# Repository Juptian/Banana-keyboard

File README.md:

# banana
* Keyboard Maintainer: [Sebastien Gosselin](https://github.com/Juptian)
* Custom PCB, built on an arduino promicro ATmega32u4
* Hardware Availability: Aliexpress has some go you'll find them for cheap

Make example for this keyboard (after setting up your build environment):

    make banana:default

Flashing example for this keyboard:

    make banana:default:flash

See the [build environment setup](https://docs.qmk.fm/#/getting_started_build_tools) and the [make instructions](https://docs.qmk.fm/#/getting_started_make_guide) for more information. Brand new to QMK? Start with our [Complete Newbs Guide](https://docs.qmk.fm/#/newbs).

## Bootloader

Enter the bootloader in 1 way:

* **Physical reset button**: Briefly press the button on the back of the PCB - some may have pads you must short instead

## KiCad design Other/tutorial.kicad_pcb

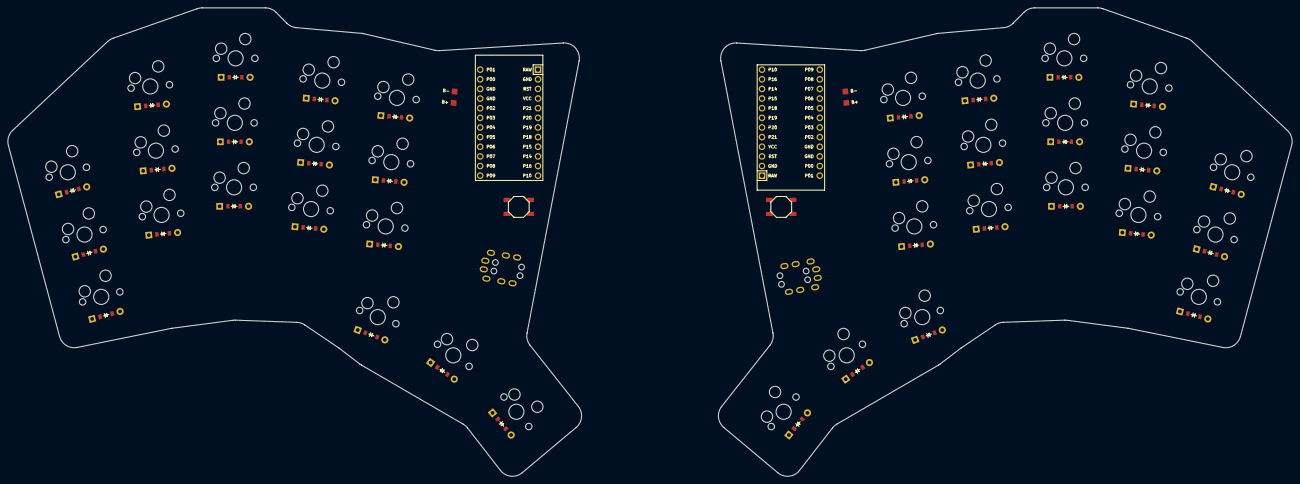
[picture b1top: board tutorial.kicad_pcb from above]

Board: 2 copper layers, 338.5 x 123.5 mm, 82 parts (0 on the bottom side), 58 nets, no tracks yet.

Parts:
B1, B2: SW_TACT_ALPS_SKQGABE010
D1, D2, D3, D4, D5, D6, D7, D8, D9, D10, D11, D12, D13, D14, D15, D16, D17, D18, D19, D20, D21, D22, D23, D24, D25, D26, D27, D28, D29, D30, D31, D32, D33, D34, D35, D36: ComboDiode
MCU1, MCU2: ProMicro
PAD1, PAD2, PAD3, PAD4: SMDPad
S1, S2, S3, S4, S5, S6, S7, S8, S9, S10, S11, S12, S13, S14, S15, S16, S17, S18, S19, S20, S21, S22, S23, S24, S25, S26, S27, S28, S29, S30, S31, S32, S33, S34, S35, S36: MX
TRRS1, TRRS2: TRRS-PJ-320A-dual

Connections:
Bplus: PAD1.1, PAD3.1
GND: B1.1, B2.1, MCU1.2, MCU1.15, MCU1.16, MCU2.2, MCU2.15, MCU2.16, PAD2.1, PAD4.1, TRRS1.3, TRRS2.3
P0: MCU1.14, MCU2.14, TRRS1.4, TRRS2.4
P1: MCU1.13, MCU2.13
P2: MCU1.17, MCU2.17
P8: MCU1.23, MCU2.23
P9: MCU1.24, MCU2.24
P10: MCU1.12, MCU2.12
P16: MCU1.11, MCU2.11
P21: MCU1.5, MCU2.5
RAW: MCU1.1, MCU2.1
RST: B1.2, B2.2, MCU1.3, MCU2.3
VCC: MCU1.4, MCU2.4, TRRS1.2, TRRS2.2
col_index: MCU1.7, MCU2.19, S10.2, S11.2, S12.2, S17.2, S28.2, S29.2, S30.2, S35.2
col_inner: MCU1.6, MCU2.18, S13.2, S14.2, S15.2, S18.2, S31.2, S32.2, S33.2, S36.2
col_middle: MCU1.8, MCU2.20, S7.2, S8.2, S9.2, S16.2, S25.2, S26.2, S27.2, S34.2
col_pinky: MCU1.10, MCU2.22, S1.2, S2.2, S3.2, S19.2, S20.2, S21.2
col_ring: MCU1.9, MCU2.21, S4.2, S5.2, S6.2, S22.2, S23.2, S24.2
first_only: D16.2, S16.1
index_bottom: D10.2, S10.1
index_home: D11.2, S11.1
index_top: D12.2, S12.1
inner_bottom: D13.2, S13.1
inner_home: D14.2, S14.1
inner_top: D15.2, S15.1
middle_bottom: D7.2, S7.1
middle_home: D8.2, S8.1
middle_top: D9.2, S9.1
mirror_first_only: D34.2, S34.1
mirror_index_bottom: D28.2, S28.1
mirror_index_home: D29.2, S29.1
mirror_index_top: D30.2, S30.1
mirror_inner_bottom: D31.2, S31.1
mirror_inner_home: D32.2, S32.1
mirror_inner_top: D33.2, S33.1
mirror_middle_bottom: D25.2, S25.1
mirror_middle_home: D26.2, S26.1
mirror_middle_top: D27.2, S27.1
mirror_pinky_bottom: D19.2, S19.1
mirror_pinky_home: D20.2, S20.1
mirror_pinky_top: D21.2, S21.1
mirror_ring_bottom: D22.2, S22.1
mirror_ring_home: D23.2, S23.1
mirror_ring_top: D24.2, S24.1
mirror_second_only: D35.2, S35.1
mirror_third_only: D36.2, S36.1
pinky_bottom: D1.2, S1.1
pinky_home: D2.2, S2.1
pinky_top: D3.2, S3.1
ring_bottom: D4.2, S4.1
ring_home: D5.2, S5.1
ring_top: D6.2, S6.1
row_bot: D1.1, D4.1, D7.1, D10.1, D13.1, D19.1, D22.1, D25.1, D28.1, D31.1, MCU1.21, MCU2.9
row_mid: D2.1, D5.1, D8.1, D11.1, D14.1, D20.1, D23.1, D26.1, D29.1, D32.1, MCU1.20, MCU2.8
row_thumb: D16.1, D17.1, D18.1, D34.1, D35.1, D36.1, MCU1.22, MCU2.10
row_top: D3.1, D6.1, D9.1, D12.1, D15.1, D21.1, D24.1, D27.1, D30.1, D33.1, MCU1.19, MCU2.7
second_only: D17.2, S17.1
third_only: D18.2, S18.1
